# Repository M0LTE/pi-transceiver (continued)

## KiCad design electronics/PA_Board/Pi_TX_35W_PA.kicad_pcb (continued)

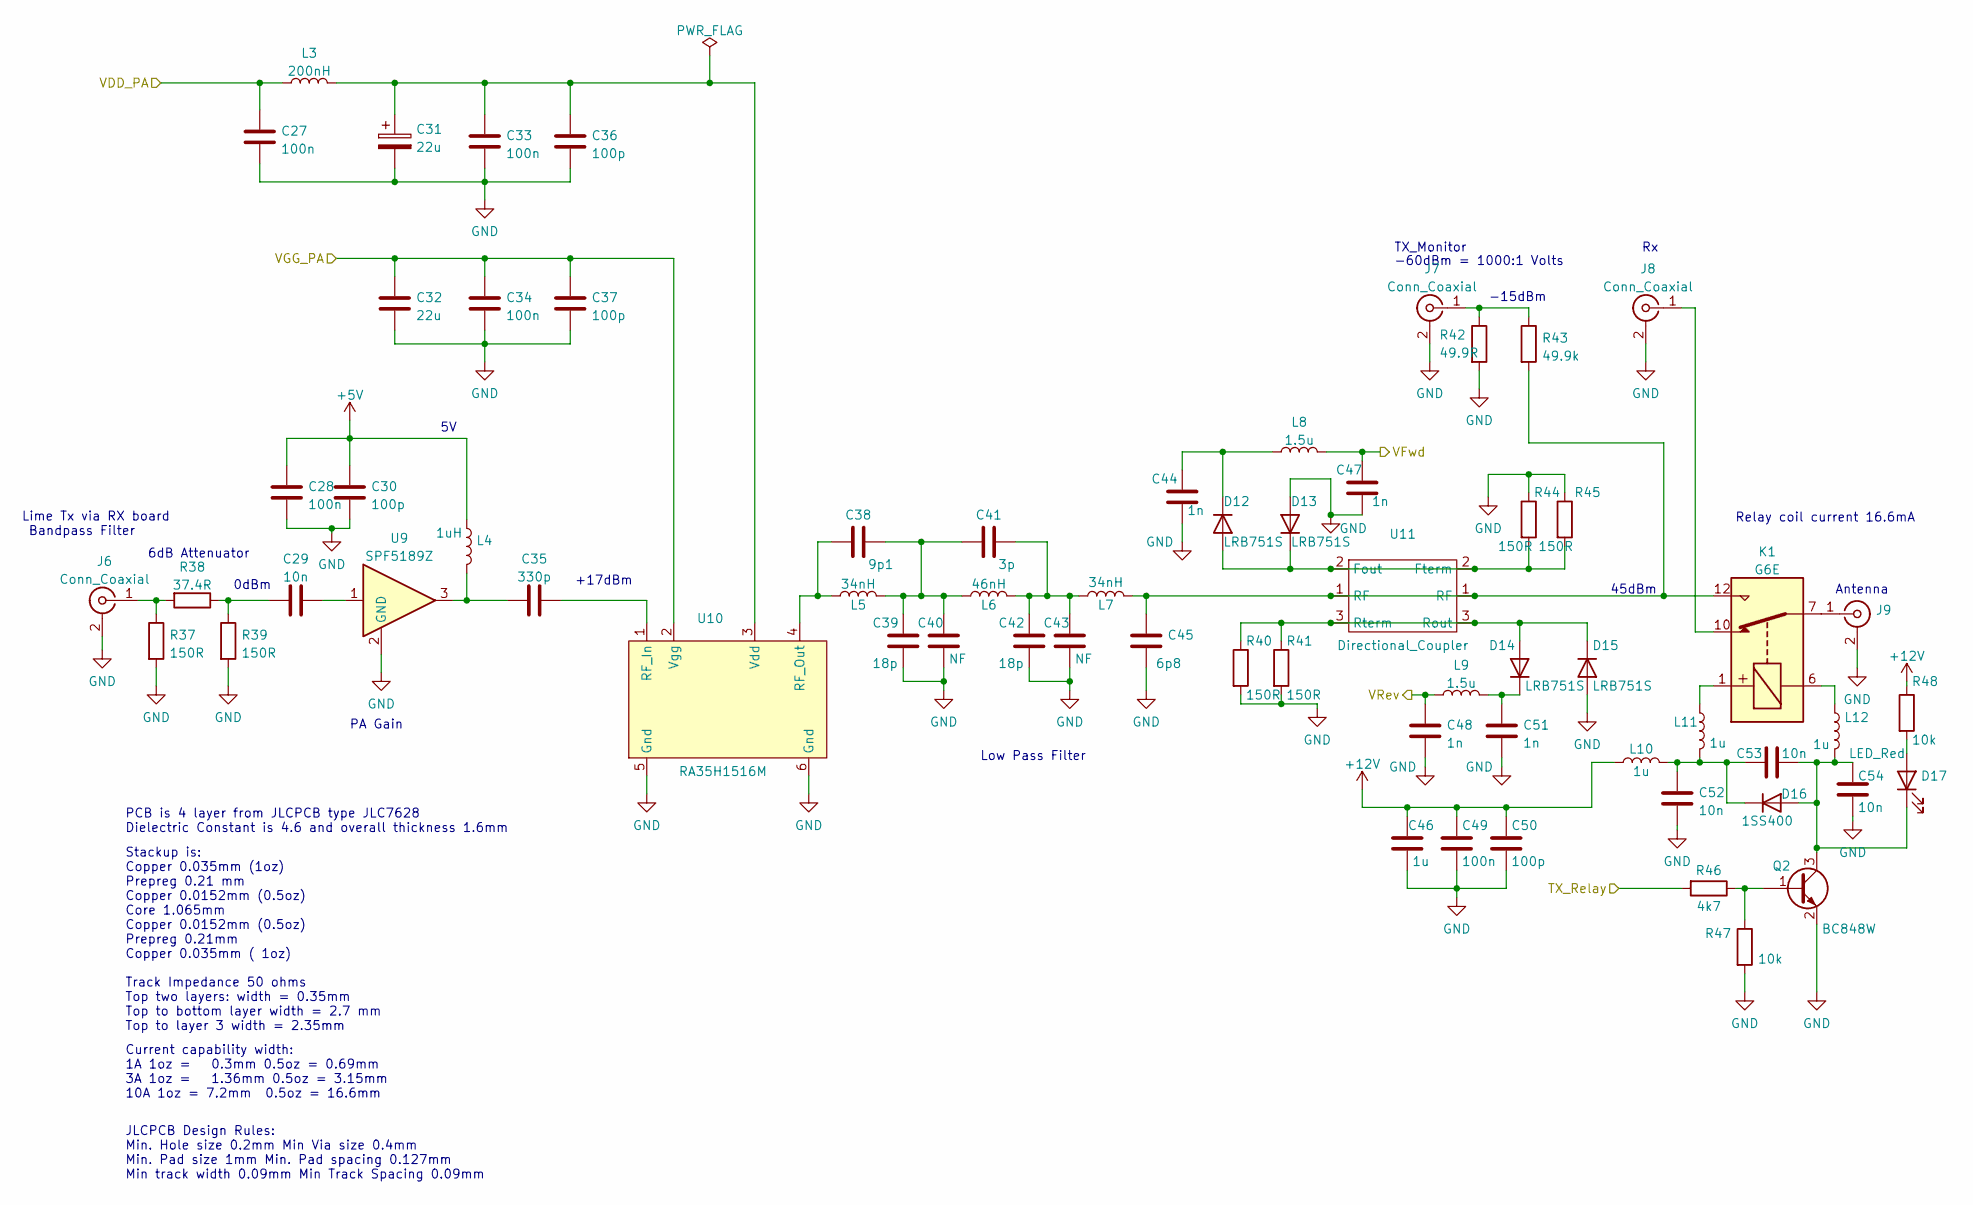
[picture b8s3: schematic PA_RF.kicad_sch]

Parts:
C27, C28, C33, C34, C49: 100n; C_0603_1608Metric
C29, C52, C53, C54: 10n; C_0603_1608Metric
C30, C36, C37, C50: 100p; C_0603_1608Metric
C31: 22u; CP_EIA-7360-38_Kemet-E
C32: 22u; C_0805_2012Metric
C35: 330p; C_0603_1608Metric
C38: 9p1; L_1206_3216Metric
C39, C42: 18p; L_1206_3216Metric
C40, C43: NF; L_1206_3216Metric
C41: 3p; L_1206_3216Metric
C44, C47, C48, C51: 1n; C_0603_1608Metric
C45: 6p8; L_1206_3216Metric
C46: 1u; C_0603_1608Metric
D12, D13, D14, D15: LRB751S; D_SOD-523
D16: 1SS400; D_SOD-523
D17: LED_Red; LED_0603_1608Metric
J6, J7, J8, J9: Conn_Coaxial; SMA_Samtec_SMA-J-P-X-ST-EM1_EdgeMount
K1: G6E; Relay_SPDT_Omron_G6E
L3: 200nH; L_1812_4532Metric
L4: 1uH; L_0805_2012Metric
L5, L7: 34nH; Wire_Inductor 12x8.5
L6: 46nH; Wire_Inductor 15.5x8.5
L8, L9: 1.5u; L_0805_2012Metric
L10, L11, L12: 1u; L_0805_2012Metric
Q2: BC848W; SOT-23
R37, R39, R40, R41, R44, R45: 150R; R_0603_1608Metric
R38: 37.4R; R_0603_1608Metric
R42: 49.9R; R_0603_1608Metric
R43: 49.9k; R_0603_1608Metric
R46: 4k7; R_0603_1608Metric
R47, R48: 10k; R_0603_1608Metric
U9: SPF5189Z; SOT-89-3
U10: RA35H1516M; RF_PA_Module
U11: Directional_Coupler; Wiggly Coupler

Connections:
+5V: C28.2, C30.2, L4.1; also elsewhere on the board
+12V: C46.1, C49.1, C50.1, L10.1, R48.1; also elsewhere on the board
/PA_Power/VDD_PA: C27.1, L3.1; also elsewhere on the board
/PA_Power/VGG_PA: C32.1, C34.1, C37.1, U10.2 (Vgg); also elsewhere on the board
/PA_Protection/TX_Relay: R46.2; also elsewhere on the board
/PA_Protection/VFwd: C47.1, L8.2; also elsewhere on the board
/PA_Protection/VRev: C48.1, L9.1; also elsewhere on the board
GND: C27.2, C28.1, C30.1, C31.2, C32.2, C33.2, C34.2, C36.2, C37.2, C39.2, C40.2, C42.2, C43.2, C44.2, C45.2, C46.2, C47.2, C48.2, C49.2, C50.2, C51.2, C52.2, C54.2, D13.2 (A), D15.2 (A), J6.2 (Ext), J7.2 (Ext), J8.2 (Ext), J9.2 (Ext), Q2.2 (E), R37.2, R39.2, R40.2, R41.2, R42.2, R44.1, R45.1, R47.2, U9.2 (GND), U10.5 (Gnd), U10.6 (Gnd); also elsewhere on the board
unnamed: C29.1, U9.1
unnamed: C29.2, R38.1, R39.1
unnamed: C31.1, C33.1, C36.1, L3.2, U10.3 (Vdd)
unnamed: C35.1, U10.1 (RF_In)
unnamed: C35.2, L4.2, U9.3
unnamed: C38.1, L5.1, U10.4 (RF_Out)
unnamed: C38.2, C39.1, C40.1, C41.1, L5.2, L6.1
unnamed: C41.2, C42.1, C43.1, L6.2, L7.1
unnamed: C44.1, D12.1 (K), L8.1
unnamed: C45.1, K1.12, L7.2, R43.2, U11.1 (RF)
unnamed: C51.1, D14.1 (K), L9.2
unnamed: C52.1, C53.2, D16.1 (K), L10.2, L11.2
unnamed: C53.1, C54.1, D16.2 (A), D17.1 (K), L12.2, Q2.3 (C)
unnamed: D12.2 (A), D13.1 (K), R44.2, R45.2, U11.2 (Fterm)
unnamed: D14.2 (A), D15.1 (K), R40.1, R41.1, U11.3 (Rout)
unnamed: D17.2 (A), R48.2
unnamed: J6.1 (In), R37.1, R38.2
unnamed: J7.1 (In), R42.1, R43.1
unnamed: J8.1 (In), K1.10
unnamed: J9.1 (In), K1.7
unnamed: K1.1, L11.1
unnamed: K1.6, L12.1
unnamed: Q2.1 (B), R46.1, R47.1

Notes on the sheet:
6dB Attenuator
JLCPCB Design Rules: Min. Hole size 0.2mm Min Via size 0.4mm Min. Pad size 1mm Min. Pad spacing 0.127mm Min track width 0.09mm Min Track Spacing 0.09mm
+17dBm
Stackup is: Copper 0.035mm (1oz) Prepreg 0.21 mm Copper 0.0152mm (0.5oz) Core 1.065mm Copper 0.0152mm (0.5oz) Prepreg 0.21mm Copper 0.035mm ( 1oz)
Current capability width: 1A 1oz = 0.3mm 0.5oz = 0.69mm 3A 1oz = 1.36mm 0.5oz = 3.15mm 10A 1oz = 7.2mm 0.5oz = 16.6mm
Antenna
PA Gain
TX_Monitor
45dBm
Lime Tx via RX board Bandpass Filter
0dBm
Low Pass Filter
-60dBm = 1000:1 Volts
-15dBm
Track Impedance 50 ohms Top two layers: width = 0.35mm Top to bottom layer width = 2.7 mm Top to layer 3 width = 2.35mm
Relay coil current 16.6mA
PCB is 4 layer from JLCPCB type JLC7628 Dielectric Constant is 4.6 and overall thickness 1.6mm

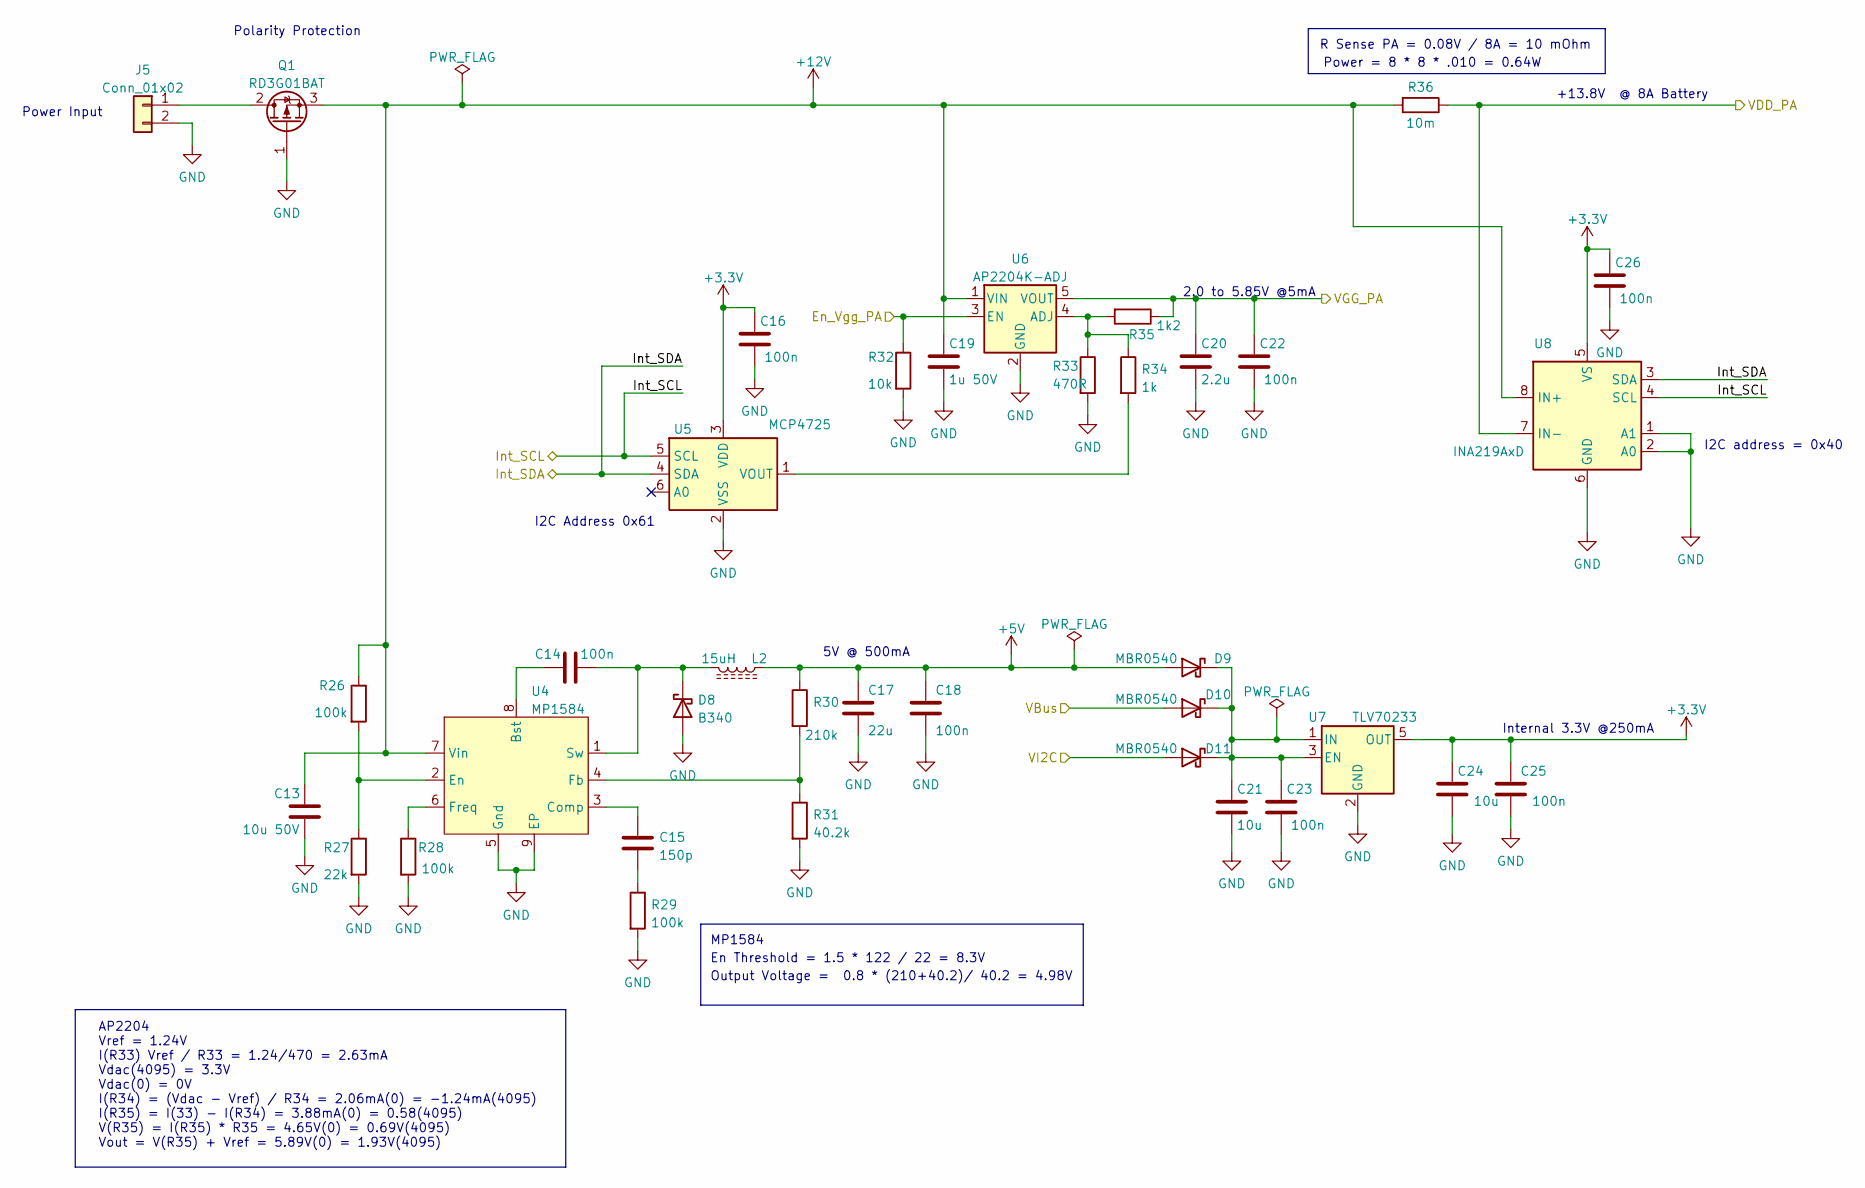
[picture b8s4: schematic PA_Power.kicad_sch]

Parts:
C13: 10u 50V; C_0805_2012Metric
C14, C16, C18, C22, C23, C25, C26: 100n; C_0603_1608Metric
C15: 150p; C_0603_1608Metric
C17: 22u; C_0805_2012Metric
C19: 1u 50V; C_0603_1608Metric
C20: 2.2u; C_0603_1608Metric
C21, C24: 10u; C_0603_1608Metric
D8: B340; D_SMA
D9, D10, D11: MBR0540; D_SOD-123
J5: Conn_01x02; PhoenixContact_MSTBA_2,5_2-G_1x02_P5.00mm_Horizontal
L2: 15uH; L_7.3x7.3_H4.5
Q1: RD3G01BAT; TO-252-2
R26, R28, R29: 100k; R_0603_1608Metric
R27: 22k; R_0603_1608Metric
R30: 210k; R_0603_1608Metric
R31: 40.2k; R_0603_1608Metric
R32: 10k; R_0603_1608Metric
R33: 470R; R_0603_1608Metric
R34: 1k; R_0603_1608Metric
R35: 1k2; R_0603_1608Metric
R36: 10m; R_0612_1632Metric
U4: MP1584; SOIC-8-1EP_3.9x4.9mm_P1.27mm_EP2.41x3.3mm
U5: MCP4725; SOT-23-6
U6: AP2204K-ADJ; SOT-23-5
U7: TLV70233; SOT-23-5
U8: INA219AxD; SOIC-8_3.9x4.9mm_P1.27mm

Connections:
+3.3V: C16.1, C24.1, C25.1, C26.1, U5.3 (VDD), U7.5 (OUT), U8.5 (VS); also elsewhere on the board
+5V: C17.1, C18.1, D9.2 (A), L2.1, R30.1; also elsewhere on the board
+12V: C13.1, C19.1, Q1.3 (S), R26.1, R36.2, U4.7 (Vin), U6.1 (VIN), U8.8 (IN+); also elsewhere on the board
/PA_Power/En_Vgg_PA: R32.1, U6.3 (EN); also elsewhere on the board
/PA_Power/Int_SCL: U5.5 (SCL), U8.4 (SCL); also elsewhere on the board
/PA_Power/Int_SDA: U5.4 (SDA), U8.3 (SDA); also elsewhere on the board
/PA_Power/VBus: D10.2 (A); also elsewhere on the board
/PA_Power/VDD_PA: R36.1, U8.7 (IN-); also elsewhere on the board
/PA_Power/VGG_PA: C20.1, C22.1, R35.1, U6.5 (VOUT); also elsewhere on the board
/PA_Power/VI2C: D11.2 (A); also elsewhere on the board
GND: C13.2, C16.2, C17.2, C18.2, C19.2, C20.2, C21.2, C22.2, C23.2, C24.2, C25.2, C26.2, D8.2 (A), J5.2, Q1.1 (G), R27.2, R28.2, R29.2, R31.2, R32.2, R33.2, U4.5 (Gnd), U4.9 (EP), U5.2 (VSS), U6.2 (GND), U7.2 (GND), U8.1 (A1), U8.2 (A0), U8.6 (GND); also elsewhere on the board
unnamed: C14.1, D8.1 (K), L2.2, U4.1 (Sw)
unnamed: C14.2, U4.8 (Bst)
unnamed: C15.1, U4.3 (Comp)
unnamed: C15.2, R29.1
unnamed: C21.1, C23.1, D9.1 (K), D10.1 (K), D11.1 (K), U7.1 (IN), U7.3 (EN)
unnamed: J5.1, Q1.2 (D)
unnamed: R26.2, R27.1, U4.2 (En)
unnamed: R28.1, U4.6 (Freq)
unnamed: R30.2, R31.1, U4.4 (Fb)
unnamed: R33.1, R34.1, R35.2, U6.4 (ADJ)
unnamed: R34.2, U5.1 (VOUT)

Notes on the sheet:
5V @ 500mA
Power Input
2.0 to 5.85V @5mA
I2C Address 0x61
+13.8V @ 8A Battery
I2C address = 0x40
MP1584
Internal 3.3V @250mA
AP2204 Vref = 1.24V I(R33) Vref / R33 = 1.24/470 = 2.63mA Vdac(4095) = 3.3V Vdac(0) = 0V I(R34) = (Vdac - Vref) / R34 = 2.06mA(0) = -1.24mA(4095) I(R35) = I(33) - I(R34) = 3.88mA(0) = 0.58(4095) V(R35) = I(R35) * R35 = 4.65V(0) = 0.69V(4095) Vout = V(R35) + Vref = 5.89V(0) = 1.93V(4095)
R Sense PA = 0.08V / 8A = 10 mOhm
Polarity Protection
Power = 8 * 8 * .010 = 0.64W
Output Voltage = 0.8 * (210+40.2)/ 40.2 = 4.98V
En Threshold = 1.5 * 122 / 22 = 8.3V

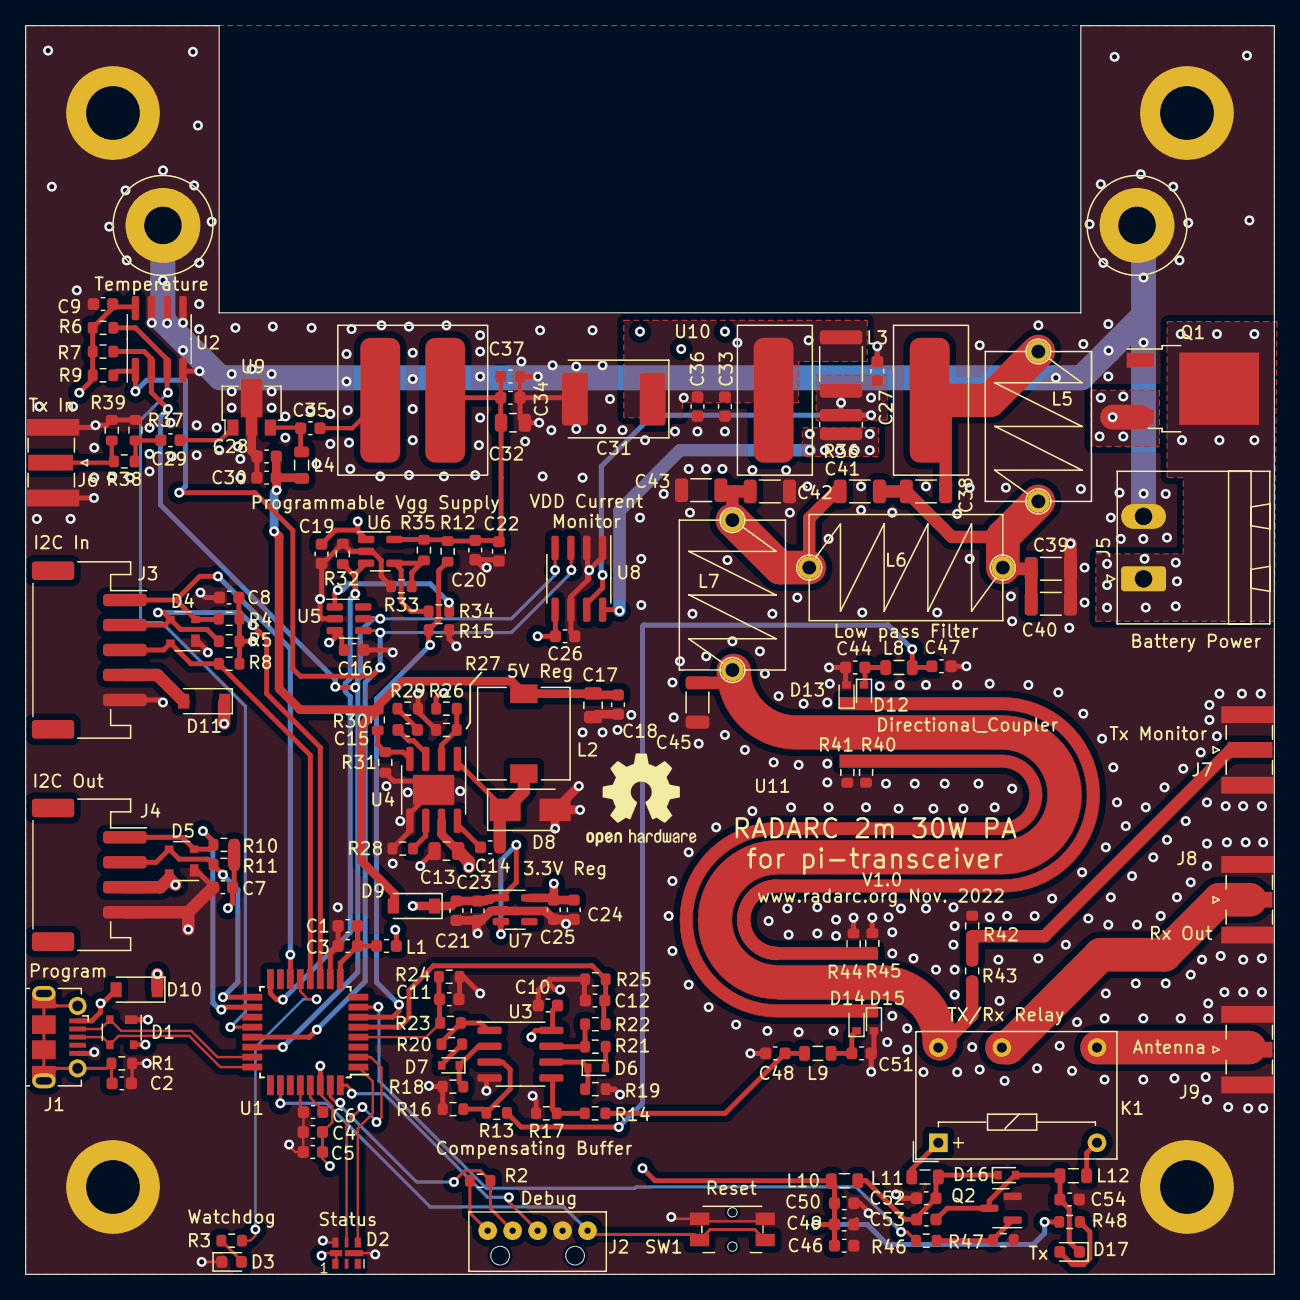
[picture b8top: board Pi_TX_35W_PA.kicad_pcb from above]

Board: 4 copper layers, 100.0 x 100.0 mm, 161 parts (1 on the bottom side), 77 nets.

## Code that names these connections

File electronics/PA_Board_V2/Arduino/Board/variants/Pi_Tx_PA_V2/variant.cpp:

/*
  Copyright (c) 2014-2015 Arduino LLC.  All right reserved.

  This library is free software; you can redistribute it and/or
  modify it under the terms of the GNU Lesser General Public
  License as published by the Free Software Foundation; either
  version 2.1 of the License, or (at your option) any later version.

  This library is distributed in the hope that it will be useful,
  but WITHOUT ANY WARRANTY; without even the implied warranty of
  MERCHANTABILITY or FITNESS FOR A PARTICULAR PURPOSE.
  See the GNU Lesser General Public License for more details.

  You should have received a copy of the GNU Lesser General Public
  License along with this library; if not, write to the Free Software
  Foundation, Inc., 51 Franklin St, Fifth Floor, Boston, MA  02110-1301  USA
*/

#include "variant.h"

/*
 * Pins descriptions
 *---------------------------------------
 * Note these are not standard Arduino pin allocations
 *---------------------------------------
 */
const PinDescription g_APinDescription[]=
{
  // 0 - SK6812 LED Data
  // ----------------------
  { PORTA, 0, PIO_DIGITAL, PIN_ATTR_DIGITAL, No_ADC_Channel, NOT_ON_PWM, NOT_ON_TIMER, EXTERNAL_INT_NONE }, // SK6812_DATA

 // 1..3 - Analog pins
  // --------------------
  { PORTA,  3, PIO_ANALOG, 0, ADC_Channel1, NOT_ON_PWM, NOT_ON_TIMER, EXTERNAL_INT_NONE }, // ADC/AIN[1] ADC_FWD
  { PORTA,  4, PIO_ANALOG, 0, ADC_Channel4, NOT_ON_PWM, NOT_ON_TIMER, EXTERNAL_INT_NONE }, // ADC/AIN[4] ADC_Rev
  { PORTA,  5, PIO_ANALOG, 0, ADC_Channel5, NOT_ON_PWM, NOT_ON_TIMER, EXTERNAL_INT_NONE }, // ADC/AIN[5] ADC_VGG
  
 // 4..5 - Digital
 // ----------------------
  { PORTA,  6, PIO_DIGITAL, PIN_ATTR_DIGITAL, No_ADC_Channel, NOT_ON_PWM, NOT_ON_TIMER, EXTERNAL_INT_NONE }, // TX RELAY
  { PORTA,  7, PIO_DIGITAL, PIN_ATTR_DIGITAL, No_ADC_Channel, NOT_ON_PWM, NOT_ON_TIMER, EXTERNAL_INT_NONE }, // DRIVER_EN

 // 6..7 Pi Serial Interface Pins to Pi
  { PORTA, 8, PIO_SERCOM, PIN_ATTR_DIGITAL, No_ADC_Channel, NOT_ON_PWM, NOT_ON_TIMER, EXTERNAL_INT_NONE }, // PI_TXD: SERCOM0/PAD[0]
  { PORTA, 9, PIO_SERCOM, PIN_ATTR_DIGITAL, No_ADC_Channel, NOT_ON_PWM, NOT_ON_TIMER, EXTERNAL_INT_NONE }, // PI_RXD: SERCOM0/PAD[1]

 // 8..11 Digital
  { PORTA, 10, PIO_DIGITAL, PIN_ATTR_DIGITAL, No_ADC_Channel, NOT_ON_PWM, NOT_ON_TIMER, EXTERNAL_INT_NONE }, // WATCHDOG_LED
  { PORTA, 11, PIO_DIGITAL, PIN_ATTR_DIGITAL, No_ADC_Channel, NOT_ON_PWM, NOT_ON_TIMER, EXTERNAL_INT_NONE }, // PI_TXEN
  { PORTA, 14, PIO_DIGITAL, PIN_ATTR_DIGITAL, No_ADC_Channel, NOT_ON_PWM, NOT_ON_TIMER, EXTERNAL_INT_14 }, // FAN_RPM
  { PORTA, 15, PIO_DIGITAL, PIN_ATTR_DIGITAL, No_ADC_Channel, NOT_ON_PWM, NOT_ON_TIMER, EXTERNAL_INT_NONE }, // EN VGG_PA

 // 12..13 External I2C pins (SDA/SCL)  
  { PORTA, 16, PIO_SERCOM, PIN_ATTR_DIGITAL, No_ADC_Channel, NOT_ON_PWM, NOT_ON_TIMER, EXTERNAL_INT_NONE }, // EXT_SDA: SERCOM1/PAD[0]
  { PORTA, 17, PIO_SERCOM, PIN_ATTR_DIGITAL, No_ADC_Channel, NOT_ON_PWM, NOT_ON_TIMER, EXTERNAL_INT_NONE }, // EXT_SCL: SERCOM1/PAD[1]
  
 // 14..15 Digital
  { PORTA, 18, PIO_DIGITAL, PIN_ATTR_DIGITAL, No_ADC_Channel, NOT_ON_PWM, NOT_ON_TIMER, EXTERNAL_INT_NONE }, // FAN_PWM
  { PORTA, 19, PIO_DIGITAL, PIN_ATTR_DIGITAL, No_ADC_Channel, NOT_ON_PWM, NOT_ON_TIMER, EXTERNAL_INT_3 }, // LM75_INT


 // 16..17 Internal I2C pins (SDA/SCL)  
  { PORTA, 22, PIO_SERCOM, PIN_ATTR_DIGITAL, No_ADC_Channel, NOT_ON_PWM, NOT_ON_TIMER, EXTERNAL_INT_NONE }, // INT_SDA: SERCOM3/PAD[0]
  { PORTA, 23, PIO_SERCOM, PIN_ATTR_DIGITAL, No_ADC_Channel, NOT_ON_PWM, NOT_ON_TIMER, EXTERNAL_INT_NONE }, // INT_SCL: SERCOM3/PAD[1]


 // 18..20 - USB
  // --------------------
  { PORTA, 24, PIO_COM, PIN_ATTR_NONE, No_ADC_Channel, NOT_ON_PWM, NOT_ON_TIMER, EXTERNAL_INT_NONE }, // USB/DM
  { PORTA, 25, PIO_COM, PIN_ATTR_NONE, No_ADC_Channel, NOT_ON_PWM, NOT_ON_TIMER, EXTERNAL_INT_NONE }, // USB/DP
  { PORTA, 28, PIO_COM, PIN_ATTR_NONE, No_ADC_Channel, NOT_ON_PWM, NOT_ON_TIMER, EXTERNAL_INT_NONE }, // USB Host enable
 
} ;



// Multi-serial objects instantiation
SERCOM sercom0( SERCOM0 ) ;
SERCOM sercom1( SERCOM1 ) ;
SERCOM sercom3( SERCOM3 ) ;


Uart Serial1( &sercom0, PIN_SERIAL1_RX, PIN_SERIAL1_TX, PAD_SERIAL1_RX, PAD_SERIAL1_TX ) ;

void SERCOM0_Handler()
{
  Serial1.IrqHandler();
}

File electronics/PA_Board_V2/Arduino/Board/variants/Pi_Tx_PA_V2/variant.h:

/*
  Copyright (c) 2014-2015 Arduino LLC.  All right reserved.

  This library is free software; you can redistribute it and/or
  modify it under the terms of the GNU Lesser General Public
  License as published by the Free Software Foundation; either
  version 2.1 of the License, or (at your option) any later version.

  This library is distributed in the hope that it will be useful,
  but WITHOUT ANY WARRANTY; without even the implied warranty of
  MERCHANTABILITY or FITNESS FOR A PARTICULAR PURPOSE.
  See the GNU Lesser General Public License for more details.

  You should have received a copy of the GNU Lesser General Public
  License along with this library; if not, write to the Free Software
  Foundation, Inc., 51 Franklin St, Fifth Floor, Boston, MA  02110-1301  USA
*/

#ifndef _VARIANT_Pi_Tx_PA_
#define _VARIANT_Pi_Tx_PA_

// The definitions here needs a SAMD core >=1.6.10
#define ARDUINO_SAMD_VARIANT_COMPLIANCE 10610

/*----------------------------------------------------------------------------
 *        Definitions
 *----------------------------------------------------------------------------*/

/** Frequency of the board main oscillator */
#define VARIANT_MAINOSC		(32768ul)

/** Master clock frequency */
#define VARIANT_MCK	(F_CPU)

/*----------------------------------------------------------------------------
 *        Headers
 *----------------------------------------------------------------------------*/

#include "WVariant.h"
#ifdef __cplusplus
#include "SERCOM.h"
#include "Uart.h"
#endif // __cplusplus

#ifdef __cplusplus
extern "C"
{
#endif // __cplusplus

/*----------------------------------------------------------------------------
 *        Pins
 *----------------------------------------------------------------------------*/

// Number of pins defined in PinDescription array
#define PINS_COUNT           (21u)
#define NUM_DIGITAL_PINS     (15u)
#define NUM_ANALOG_INPUTS    (3u)
#define NUM_ANALOG_OUTPUTS   (0u)
#define analogInputToDigitalPin(p)  ((p < 3u) ? (p) + PIN_A0 : -1)

#define digitalPinToPort(P)        ( &(PORT->Group[g_APinDescription[P].ulPort]) )
#define digitalPinToBitMask(P)     ( 1 << g_APinDescription[P].ulPin )
#define portOutputRegister(port)   ( &(port->OUT.reg) )
#define portInputRegister(port)    ( &(port->IN.reg) )
#define portModeRegister(port)     ( &(port->DIR.reg) )
#define digitalPinHasPWM(P)        ( g_APinDescription[P].ulPWMChannel != NOT_ON_PWM || g_APinDescription[P].ulTCChannel != NOT_ON_TIMER )



// LEDs
#define PIN_LED              (8u)
#define LED_BUILTIN          PIN_LED
#define LED_WATCHDOG         PIN_LED
#define WATCHDOG_LED         PIN_LED

//  RGBW addressable LEDs
#define PIN_SK6812_DATA      (0u)
#define SK6812_NUM           (02u)

/*
 * Analog Pins
 */
#define PIN_A0               (1ul)
#define PIN_A1               (PIN_A0 + 1)
#define PIN_A2               (PIN_A0 + 2)
#define PIN_DAC0             (-1ul) // DAC not used
#define PIN_ADC_FWD          PIN_A0
#define PIN_ADC_REV          PIN_A1
#define PIN_ADC_VGG          PIN_A2

static const uint8_t A0  = PIN_A0;
static const uint8_t A1  = PIN_A1;
static const uint8_t A2  = PIN_A2;


#define ADC_RESOLUTION		12

/*
 * Digital Pins
 */
#define PIN_TX_RELAY         (4u)
#define PIN_DRIVER_EN        (5u)
#define PIN_PI_TX_EN         (9u)
#define PIN_FAN_RPM          (10u)
#define PIN_EN_VGG           (11u)
#define PIN_FAN_PWM          (14u)
#define PIN_LM75_INT         (15u)

/*
 * Serial interfaces
 */

// Serial1 (sercom 0)
#define PIN_SERIAL1_TX       (6ul) // PA08
#define PAD_SERIAL1_TX       (UART_TX_PAD_0)
#define PIN_SERIAL1_RX       (7ul) // PA09
#define PAD_SERIAL1_RX       (SERCOM_RX_PAD_1)

/*
 * SPI Interfaces
 */
#define SPI_INTERFACES_COUNT 1 // We don't use an SPI interface, but some libraries Adafruit OLED appear to need one defined

#define PIN_SPI_MISO         (-1)  // setup with dummy pins
#define PIN_SPI_MOSI         (-1)
#define PIN_SPI_SCK          (-1)
#define PERIPH_SPI           sercom0
#define PAD_SPI_TX           SPI_PAD_2_SCK_3
#define PAD_SPI_RX           SERCOM_RX_PAD_1


/*
 * Wire Interfaces
 */
#define WIRE_INTERFACES_COUNT 2

/*
 * The internal I2C Bus
 */
#define PIN_WIRE_SDA         (16u)
#define PIN_WIRE_SCL         (17u)
#define PERIPH_WIRE          sercom3
#define WIRE_IT_HANDLER      SERCOM3_Handler
static const uint8_t SDA = PIN_WIRE_SDA;
static const uint8_t SCL = PIN_WIRE_SCL;


/*
 * The external I2C Bus
 */
#define PIN_WIRE1_SDA         (12u)
#define PIN_WIRE1_SCL         (13u)
#define PERIPH_WIRE1          sercom1
#define WIRE1_IT_HANDLER      SERCOM1_Handler
static const uint8_t SDA1 = PIN_WIRE1_SDA;
static const uint8_t SCL1 = PIN_WIRE1_SCL;

/*
 * USB
 */
#define PIN_USB_HOST_ENABLE (33ul)
#define PIN_USB_DM          (34ul)
#define PIN_USB_DP          (35ul)

#ifdef __cplusplus
}
#endif

/*----------------------------------------------------------------------------
 *        Arduino objects - C++ only
 *----------------------------------------------------------------------------*/

#ifdef __cplusplus

/*	=========================
 *	===== SERCOM DEFINITION
 *	=========================
 * The ATSAMD21E18 only has four SERCOM Ports and we ony use 3 due to Pin limitations
 * SERCOM0 is Serial
 * SERCOM1 is Wire
 * SERCOM3 is Wire1
 * 
*/

extern SERCOM sercom0;
extern SERCOM sercom1;
extern SERCOM sercom3;

extern Uart Serial1;


#endif


//
// SERIAL_PORT_USBVIRTUAL     Port which is USB virtual serial
//

#define SERIAL_PORT_USBVIRTUAL      Serial
#define SERIAL_PORT_MONITOR         Serial

// Serial has no physical pins broken out, so it's not listed as HARDWARE port
#define SERIAL_PORT_HARDWARE        Serial1
#define SERIAL_PORT_HARDWARE_OPEN   Serial1

#endif /* _VARIANT_Pi_Tx_PA_ */

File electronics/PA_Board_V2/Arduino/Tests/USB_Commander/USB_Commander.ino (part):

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Adafruit_MCP4725 dac;
Adafruit_INA219 ina219;
Generic_LM75_12Bit temperature(&Wire);
Adafruit_NeoPixel RGB(SK6812_NUM, PIN_SK6812_DATA, NEO_RGB + NEO_KHZ800);
Adafruit_SSD1306 display(SCREEN_WIDTH, SCREEN_HEIGHT, &Wire1, OLED_RESET);
PCF8574 RX_BOARD(0x38, &Wire1);

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  // Connect the TCC0 timer to digital output D14 - port pins are paired odd PMUO and even PMUXE
 

  PORT->Group[g_APinDescription[PIN_FAN_PWM].ulPort].PMUX[g_APinDescription[PIN_FAN_PWM].ulPin >> 1].reg = PORT_PMUX_PMUXE_F; // D1 is on PA18 = even, use device F on TCC0/WO[2]

  // Feed GCLK4 to TCC0 and TCC1
  REG_GCLK_CLKCTRL = GCLK_CLKCTRL_CLKEN |         // Enable GCLK4 to TCC0 and TCC1
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/*
 * PA Drivers are setup and disabled
 */
  pinMode(PIN_DRIVER_EN, OUTPUT);
  digitalWrite(PIN_DRIVER_EN, LOW);
/*
 * Tx Relay drive is setup and disabled 
 */
  pinMode(PIN_TX_RELAY, OUTPUT);
  digitalWrite(PIN_TX_RELAY, LOW);

/*
 * Fan PWM is setup and fan set off
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/*
 * FAN RPM interrupt Pin is setup and attached
 */
  pinMode(PIN_FAN_RPM, INPUT);
  attachInterrupt(digitalPinToInterrupt(PIN_FAN_RPM), RPM_Pulse, FALLING);


/*
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
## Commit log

2022-01-02 Commit some folder structure
2022-01-02 Commit rig controller skeleton solution
2022-01-02 This gets a .NET 6 app running at startup and loaded into kiosk mode
2022-01-02 Minimal signalr integration
2022-01-02 Get signalR messages flowing both ways
2022-01-02 Install and prove the radio stuff
2022-01-03 VFO digits
2022-01-03 Hack together some up/down buttons
2022-01-03 Implement up and down buttons
2022-01-03 Hack in support for flex knob (#11)
2022-01-03 Tidy up UI
2022-01-03 Reduce timeout
2022-01-03 Tweaks
2022-01-03 Style the buttons a bit
2022-01-03 Add a range check (note: repeated)
2022-01-03 Don't throw.
2022-01-03 Keep the UI up to date
2022-01-03 Try to hide the cursor totally
2022-01-03 Disable bodge
2022-01-03 Add a log, fix the buttons, get an initial update at the right time
2022-01-03 Hide the cursor quicker
2022-01-03 Formatting
2022-01-03 Wait for service
2022-01-03 Avoid long press
2022-01-03 Keep the UI fast
2022-01-04 Hack in mouse X axis tuning
2022-01-04 Revert "Hack in mouse X axis tuning"
    This reverts commit 200ec5ba17e3022493f23212675e0e129de4f12e.
2022-01-04 The most basic of SSB transmitters
2022-01-04 Add DC block and LPF to flow graph, make it runnable from the command line
2022-01-04 Add audio recording test flowgraph
2022-01-04 Just a CW
2022-01-07 Update README.md (#19)
2022-01-08 Add sine flow graph with some controls
2022-01-08 Small updates
2022-01-09 Sanity check the GPIO
2022-01-09 GPIO and better .NET 6
2022-01-09 Hack in a GPIO service
2022-01-10 Rpc test (#23)
    * Create SSB_TX_RPC.grc
    * Create SSB_TX_RPC.py
2022-01-10 TX button
    Closes #3
2022-01-10 Fix locking
2022-01-10 Work on locking
2022-01-10 Remove locking for now
2022-01-10 Invert relays since we're normally in RX
2022-01-10 Unkey at startup.
2022-01-11 Keep relays de-energised all the way through boot
2022-01-12 Add gain parameter
2022-01-14 Update FlexKnob.cs
    Switched on DTR for compatibility with FlexKnob emulation on Arduino Pro Micro
2022-01-14 M0zsu encoder (#27)
    Switched on DTR for compatibility with FlexKnob emulation on Arduino Pro Micro
2022-01-15 144 MHz BPF design
    Excel spreadsheet to design 4 pole bandpass filter. 1dB bandwidth form 144 to 147 MHz.
2022-01-15 Dummy upload
2022-01-18 Create LangstoneMouse.ino
    Added initial work in progress code
2022-01-18 M0ZSU encoder (#31)
2022-01-18 Create LangstoneMouse.ino
    Testing mouse detection
2022-01-18 Create README.md (#35)
2022-01-18 Add datasheets
2022-01-18 Imported bob powerpole and upgraded to kicad 6. Also added shutdown interface and latching input mosfet
2022-01-18 Added 5.1V 3V supply
2022-01-19 Updated shutdown circuit
2022-01-19 Shutdown circuit update and 5v supply output fix
2022-01-19 Added LM2679 details and project library
2022-01-20 New PSU Design and added connectors
2022-01-20 Re-upload conflicting files
2022-01-21 Added 5V Protection. Set component ID's
2022-01-21 Generate BOM
2022-01-23 Remove hard dependency on pigs
2022-01-23 Slow down the ticks for now
2022-01-23 Basic reading of ADS1115 I2C ADC to the console every 10s (#21) (#39)
2022-01-24 Testing i2c
2022-01-24 Test
2022-01-24 Test 2
2022-01-24 Added wiringPi
2022-01-24 PCB Footprint Updates
2022-01-24 Added connects to parts list and footprint
2022-01-25 Update LangstoneMouse.ino
    Improvements, implements buttons. Note link pin 7 to ground for Flex emulation
2022-01-25 Tidying
2022-01-26 FM rx testing
2022-01-27 FM test
2022-02-03 Test UPS Hat
2022-02-03 testing.
2022-02-03 G4CDF branch (#41)
    * 144 MHz BPF design
    Excel spreadsheet to design 4 pole bandpass filter. 1dB bandwidth form 144 to 147 MHz.
    * Dummy upload
2022-02-03 Update README.md (#42)
2022-02-03 All of the changes on Gareth's branch vs current main
2022-02-03 All of the changes on Gareth's branch vs current main (#44)
2022-02-03 M0ZSU encoder (#45)
    * Update README.md
    * Update FlexKnob.cs
    Switched on DTR for compatibility with FlexKnob emulation on Arduino Pro Micro
    * Create LangstoneMouse.ino
    Added initial work in progress code
    * Create LangstoneMouse.ino
2022-02-09 Added services for DAC Meter and UPS Hat option. Try using alternative GPIO.
2022-02-09 Install notes update
2022-02-10 Test GNURadio files
2022-02-10 Added Loz NBFM test
2022-02-10 Addded some test GNUradio files (grc)
2022-02-10 Test XMLRPC
2022-02-10 Change freq
2022-02-10 Changes to GNURadio files
2022-02-10 Added test py file for narrowband fm
2022-02-10 Refactor flowgraph control service
2022-02-10 Refactor UPSHatService
2022-02-10 Rename file to match new class name
2022-02-10 Removed unused parameter
2022-02-10 Set listen interface.
2022-02-10 Don't report whole stack trace
2022-02-10 Add a native I2C device driver
2022-02-10 Implement native GPIO service
2022-02-10 Add info about I2C
2022-02-10 Don't flip relay any more
2022-02-11 Add print of UPS battery voltage
2022-02-14 Bug fix on I2C enabled check
2022-02-14 Added extra gain on WBFM test
2022-02-14 Added UPS debug output
2022-02-18 Commit i2ctest tool
2022-02-28 Added pi_transceiver_hat KiCad project
2022-03-02 Added fan sockets
2022-03-07 More PCB hat design
2022-03-11 More PCB updates
2022-03-14 More hat board design.
2022-03-15 PCB updates for hat.
2022-03-16 Hat PCB alpha design
2022-03-16 Initial commit of "bits'n_bobs" in electronics
    Added the kicad file and short README for test modules and breakouts
2022-03-16 Add .gitignore for kicad bsckups
2022-03-16 Gerber generation for hat.
2022-03-20 Start on engineering test program
2022-03-23 update pi_transceiver_hat Kicad
    Change to "all copper layers" for some connector holes
2022-03-23 Update pi_transceiver_Hat Kicad to all copper layers
    Changed to all copper layers on vias
2022-09-12 Update README.md
    Not yet finished
2022-10-04 Added BOM to hat
2022-10-06 Added DAC code
2022-10-06 DAC Debud
2022-10-31 Added PA board Kicad files
2022-11-09 PCB updates and gerbers
2022-11-15 Added fan test code for transceiver hat
2022-11-16 Supress ADC service when ADC not present.
2022-11-16 PWM testing.
2022-11-23 FanService update
2023-01-02 Update Kicad Schematic and PCB
    Fixed: D8 was reversed, Q2 wrong footprint.
    Some component values added or changed
    Documentation added
2023-01-02 Add Bootloader for Arduino
2023-01-02 Add boards files to Add Pi_Tx_PA
    Add Arduino boards file and variant for Pi_Tx_PA processor
2023-01-06 Add PA Board tests
    Add PA Board Arduino Tests
2023-01-10 Add More PA Board Arduino Tests
2023-10-30 Add fikter design files
2023-10-30 Filter
    Filter values entered
2023-10-30 Add values
2023-10-30 Backup
2023-11-03 Merge branch 'main' of https://github.com/M0LTE/pi-transceiver
    Addition of PA Board version 2 Kicad files
2023-11-03 Branch for changes to RX LNA board from M0SKP
    Upgrade files to Kicad 7
    Added Fields for comment and LCSC part numbers to symbol table
    Populated some LCSC part numbers to allow testing at JLCPCB
2023-11-08 Revert "Update RXLNA.kicad_prl"
    This reverts commit 634b977b9084e2730dbfc21feeff49dd8c106538.
2023-11-08 Change L construction
2023-11-08 Add RF Screen and some PCB and BOM changes
2023-11-09 Capacitor updates
    Updated series capacitor preferred values
2023-11-09 Update preferred capacitors
2023-11-10 Sorted filter cap calculation algorithm
2023-11-11 Add old version
    Debug simulation
2023-11-11 Differences for sim
2023-11-11 Debug sim
2023-11-11 Delete
2023-11-11 Revert "Create Filter PI.sch"
    This reverts commit 1df28eb7800bb939fc74a075d446743f0429498f.
2023-11-11 Tidy up simulation files
2023-11-12 Update filter design
    Updated schematic and simulation results
2023-11-13 Update values
2023-11-13 Update
    Schematic values
    Add some Data sheets
2023-11-15 Control definition
    Various updates and new Software interface description
2023-11-20 Ignore zip files
2023-11-24 Update software\system\README
    Move old version to -old
    Updated to cover new versions of Raspberry Pi OS, gnuradio, and limesuite
2023-11-25 Update README.md
    Add GUI setup description
2023-12-09 Various changes to Filter Design
2023-12-09 Updated simulation
2023-12-15 Latest version
2024-01-07 Add Arduino code for V2 PA Board
    New boards.txt and variants folder
    New test code for fan and new features
2024-01-07 Update PA board V2 Kicad files
    New schematic, PCB, and footprints
2024-01-07 Save unlocked Kicad files for PA Board V2
2024-03-22 Repair
    Fix Github commit problem
2024-04-04 add error handlers for i2c
2024-04-11 Update Kicad files
2024-04-11 Update PA V2 firmware files
2024-04-12 Update Arduino documentation and change to Kicad V8
2024-11-24 Updates in electronics bits and bobs
2024-11-24 Create Si4732 Pico
